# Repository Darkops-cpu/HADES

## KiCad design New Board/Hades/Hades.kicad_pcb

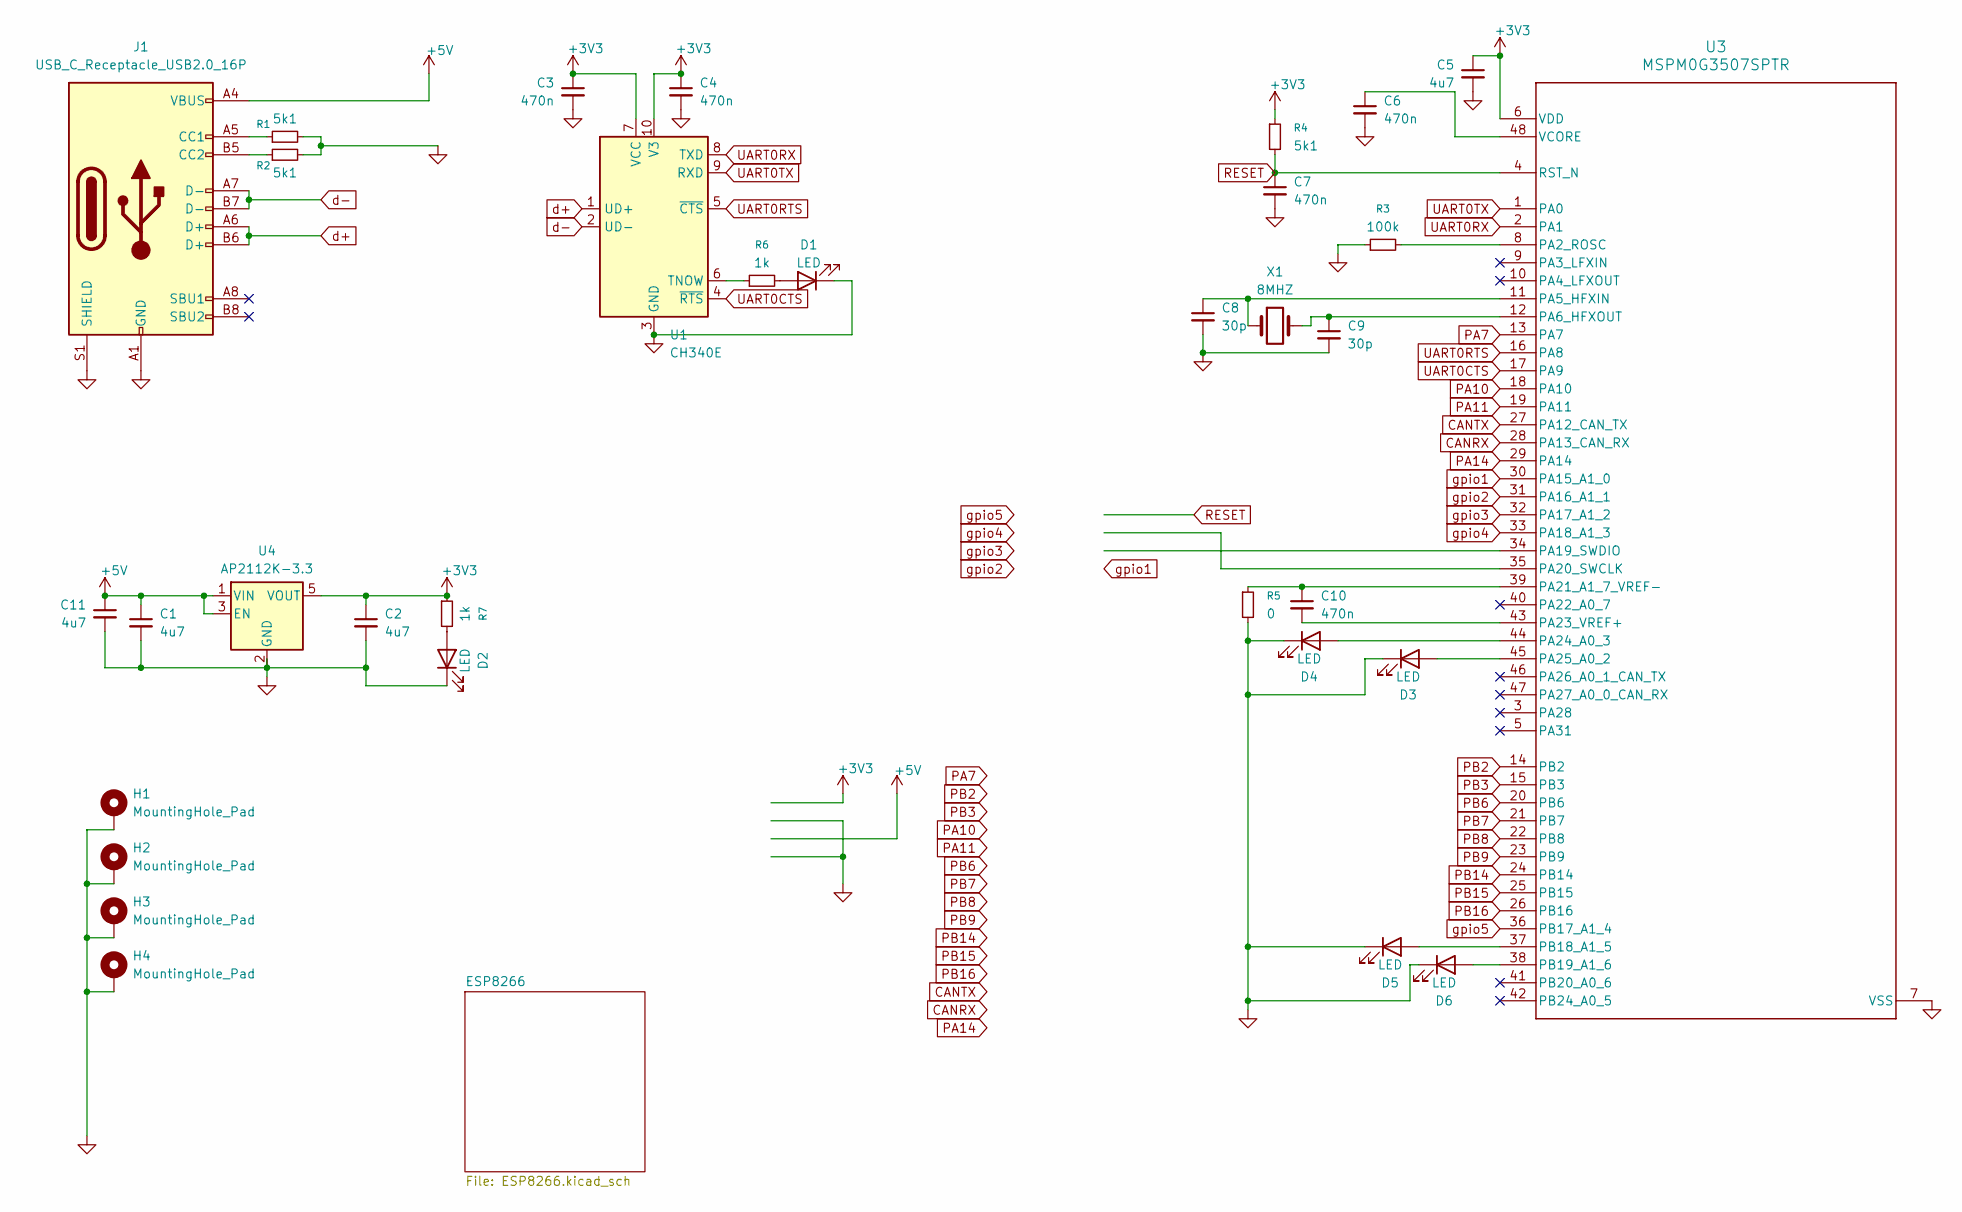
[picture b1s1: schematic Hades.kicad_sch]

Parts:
C1, C2, C5, C11: 4u7; C_0603_1608Metric
C3, C4, C6, C7, C10: 470n; C_0603_1608Metric
C8, C9: 30p; C_0603_1608Metric
D1, D2, D3, D4, D5, D6: LED; LED_0603_1608Metric
H1, H2, H3, H4: MountingHole_Pad; MountingHole_2.2mm_M2_Pad_Via
J1: USB_C_Receptacle_USB2.0_16P; USB_C_Receptacle_GCT_USB4105-xx-A_16P_TopMnt_Horizontal
R1, R2, R4: 5k1; R_0603_1608Metric
R3: 100k; R_0603_1608Metric
R5: 0; R_0603_1608Metric
R6, R7: 1k; R_0603_1608Metric
U1: CH340E; MSOP-10_3x3mm_P0.5mm
U3: MSPM0G3507SPTR; PT0048A-IPC_A
U4: AP2112K-3.3; SOT-23-5
X1: 8MHZ; Crystal_SMD_5032-2Pin_5.0x3.2mm

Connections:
+3V3: C2.1, C3.1, C4.1, C5.1, R4.1, R7.1, U1.7 (VCC), U1.10 (V3), U3.6 (VDD), U4.5 (VOUT); also elsewhere on the board
+5V: C1.1, C11.1, J1.A4 (VBUS), J1.A9 (VBUS), J1.B4 (VBUS), J1.B9 (VBUS), U4.1 (VIN), U4.3 (EN); also elsewhere on the board
CANRX: U3.28 (PA13_CAN_RX)
CANTX: U3.27 (PA12_CAN_TX)
GND: C1.2, C2.2, C3.2, C4.2, C5.2, C6.2, C7.2, C8.2, C9.2, C11.2, D1.1 (K), D2.1 (K), D3.1 (K), D4.1 (K), D5.1 (K), D6.1 (K), H1.1, H2.1, H3.1, H4.1, J1.A1 (GND), J1.A12 (GND), J1.B1 (GND), J1.B12 (GND), J1.S1 (SHIELD), R1.2, R2.2, R3.1, R5.2, U1.3 (GND), U3.7 (VSS), U4.2 (GND); also elsewhere on the board
unnamed: D1.2 (A), R6.2
unnamed: D2.2 (A), R7.2
unnamed: D3.2 (A), U3.45 (PA25_A0_2)
unnamed: D4.2 (A), U3.44 (PA24_A0_3)
unnamed: D5.2 (A), U3.37 (PB18_A1_5)
unnamed: D6.2 (A), U3.38 (PB19_A1_6)
unnamed: J1.A5 (CC1), R1.1
unnamed: J1.B5 (CC2), R2.1
unnamed: R6.1, U1.6 (TNOW)
unnamed: R3.2, U3.8 (PA2_ROSC)
unnamed: C8.1, U3.11 (PA5_HFXIN), X1.1
unnamed: C9.1, U3.12 (PA6_HFXOUT), X1.2
unnamed: C10.1, R5.1, U3.39 (PA21_A1_7_VREF-)
unnamed: C10.2, U3.43 (PA23_VREF+)
unnamed: C6.1, U3.48 (VCORE)
PA7: U3.13 (PA7)
PA10: U3.18 (PA10)
PA11: U3.19 (PA11)
PA14: U3.29 (PA14)
PB2: U3.14 (PB2)
PB3: U3.15 (PB3)
PB6: U3.20 (PB6)
PB7: U3.21 (PB7)
PB8: U3.22 (PB8)
PB9: U3.23 (PB9)
PB14: U3.24 (PB14)
PB15: U3.25 (PB15)
PB16: U3.26 (PB16)
RESET: C7.1, R4.2, U3.4 (RST_N)
UART0CTS: U1.4 (~RTS), U3.17 (PA9)
UART0RTS: U1.5 (~CTS), U3.16 (PA8)
UART0RX: U1.8 (TXD), U3.2 (PA1)
UART0TX: U1.9 (RXD), U3.1 (PA0)
d+: J1.A6 (D+), J1.B6 (D+), U1.1 (UD+)
d-: J1.A7 (D-), J1.B7 (D-), U1.2 (UD-)
gpio1: U3.30 (PA15_A1_0)
gpio2: U3.31 (PA16_A1_1)
gpio3: U3.32 (PA17_A1_2)
gpio4: U3.33 (PA18_A1_3)
gpio5: U3.36 (PB17_A1_4)

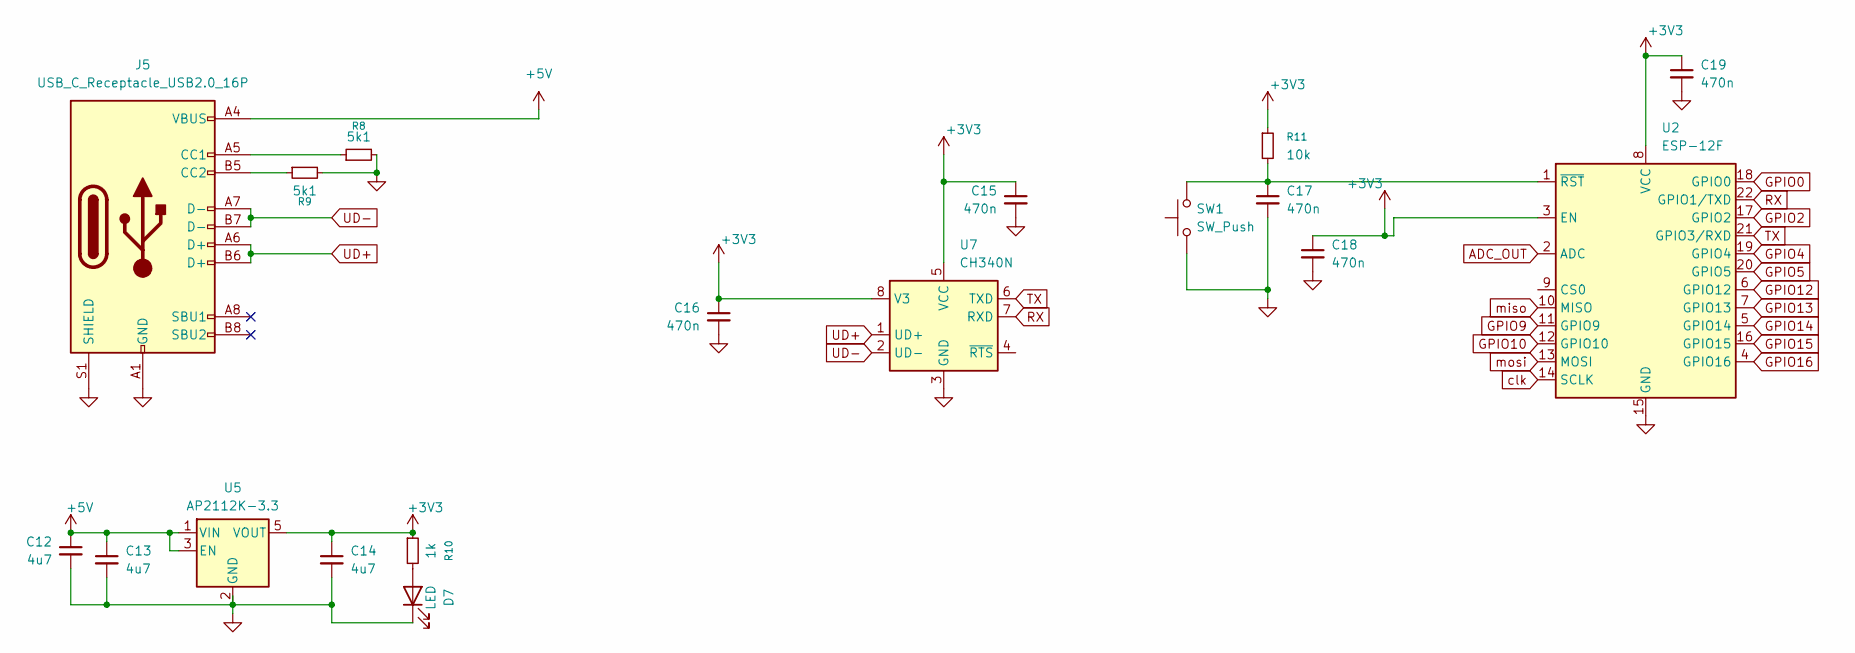
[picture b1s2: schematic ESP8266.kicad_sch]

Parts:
C12, C13, C14: 4u7; C_0603_1608Metric
C15, C16, C17, C18, C19: 470n; C_0603_1608Metric
D7: LED; LED_0603_1608Metric
J5: USB_C_Receptacle_USB2.0_16P; USB_C_Receptacle_GCT_USB4105-xx-A_16P_TopMnt_Horizontal
R8, R9: 5k1; R_0603_1608Metric
R10: 1k; R_0603_1608Metric
R11: 10k; R_0603_1608Metric
SW1: SW_Push; SW_Push_SPST_NO_Alps_SKRK
U2: ESP-12F; ESP-12E
U5: AP2112K-3.3; SOT-23-5
U7: CH340N; JEITA_SOIC-8_3.9x4.9mm_P1.27mm

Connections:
+3V3: C14.1, C15.1, C16.1, C18.1, C19.1, R10.1, R11.1, U2.3 (EN), U2.8 (VCC), U5.5 (VOUT), U7.5 (VCC), U7.8 (V3); also elsewhere on the board
+5V: C12.1, C13.1, J5.A4 (VBUS), J5.A9 (VBUS), J5.B4 (VBUS), J5.B9 (VBUS), U5.1 (VIN), U5.3 (EN); also elsewhere on the board
ADC_OUT: U2.2 (ADC)
GND: C12.2, C13.2, C14.2, C15.2, C16.2, C17.2, C18.2, C19.2, D7.1 (K), J5.A1 (GND), J5.A12 (GND), J5.B1 (GND), J5.B12 (GND), J5.S1 (SHIELD), R8.2, R9.2, SW1.1, U2.15 (GND), U5.2 (GND), U7.3 (GND); also elsewhere on the board
GPIO0: U2.18 (GPIO0)
GPIO2: U2.17 (GPIO2)
GPIO4: U2.19 (GPIO4)
GPIO5: U2.20 (GPIO5)
GPIO9: U2.11 (GPIO9)
GPIO10: U2.12 (GPIO10)
GPIO12: U2.6 (GPIO12)
GPIO13: U2.7 (GPIO13)
GPIO14: U2.5 (GPIO14)
GPIO15: U2.16 (GPIO15)
GPIO16: U2.4 (GPIO16)
unnamed: D7.2 (A), R10.2
unnamed: J5.A5 (CC1), R8.1
unnamed: J5.B5 (CC2), R9.1
unnamed: C17.1, R11.2, SW1.2, U2.1 (~RST)
RX: U2.22 (GPIO1/TXD), U7.7 (RXD)
TX: U2.21 (GPIO3/RXD), U7.6 (TXD)
UD+: J5.A6 (D+), J5.B6 (D+), U7.1 (UD+)
UD-: J5.A7 (D-), J5.B7 (D-), U7.2 (UD-)
clk: U2.14 (SCLK)
miso: U2.10 (MISO)
mosi: U2.13 (MOSI)

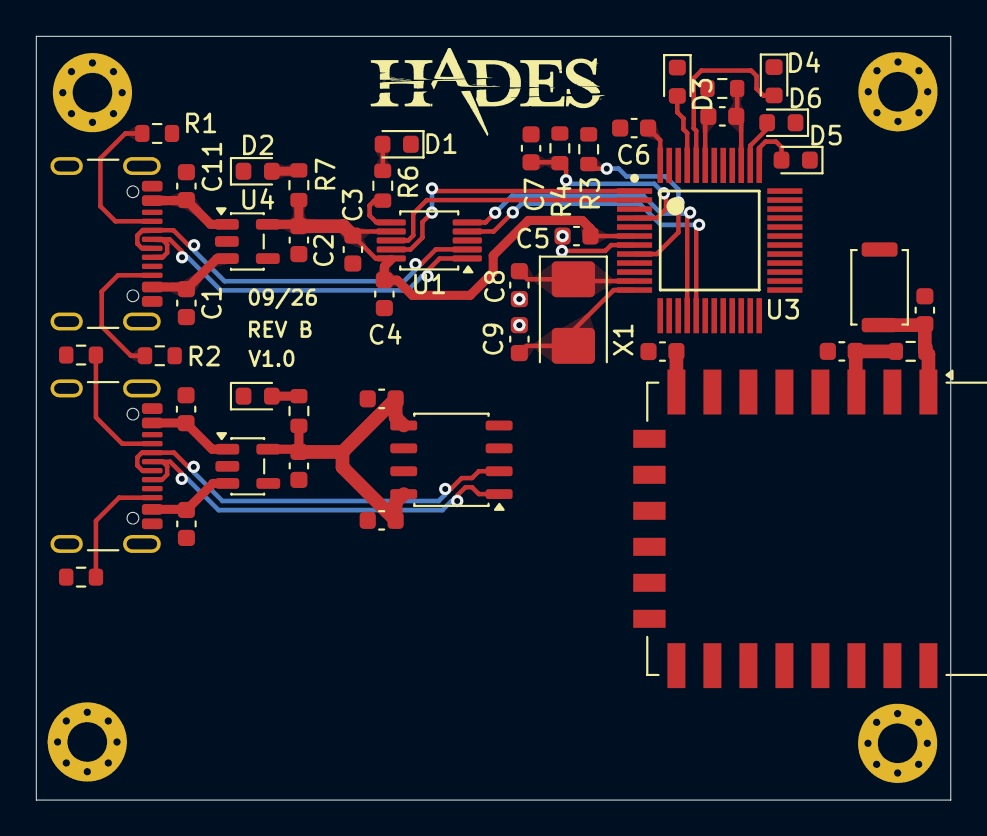
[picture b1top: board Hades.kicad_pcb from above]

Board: 2 copper layers, 50.8 x 42.4 mm, 51 parts (0 on the bottom side), 33 nets.

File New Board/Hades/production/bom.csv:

Designator,Footprint,Quantity,Value,LCSC Part #
"C1, C11, C2, C5",0603,4,4u7,
"C10, C3, C4, C6, C7",0603,5,470n,
"C8, C9",0603,2,30p,
"D1, D2",0603,2,LED,
J1,USB_C_Receptacle_GCT_USB4105-xx-A_16P_TopMnt_Horizontal,1,USB_C_Receptacle_USB2.0_16P,
J2,PinHeader_2x04_P2.54mm_Vertical,1,Conn_02x04_Odd_Even,
J3,PinHeader_1x15_P2.54mm_Vertical,1,Conn_01x15_Pin,
J4,PinHeader_1x04_P2.54mm_Vertical,1,Conn_01x04_Pin,
"R1, R2, R4",0603,3,5k1,
R3,0603,1,100k,
R5,0603,1,0,
"R6, R7",0603,2,1k,
"TP1, TP2",TestPoint_Pad_1.5x1.5mm,2,TestPoint_Probe,
U1,MSOP-10_3x3mm_P0.5mm,1,CH340E,
U3,PT0048A-IPC_A,1,MSPM0G3507SPTR,
U4,SOT-23-5,1,AP2112K-3.3,
X1,Crystal_SMD_5032-2Pin_5.0x3.2mm,1,8MHZ,
